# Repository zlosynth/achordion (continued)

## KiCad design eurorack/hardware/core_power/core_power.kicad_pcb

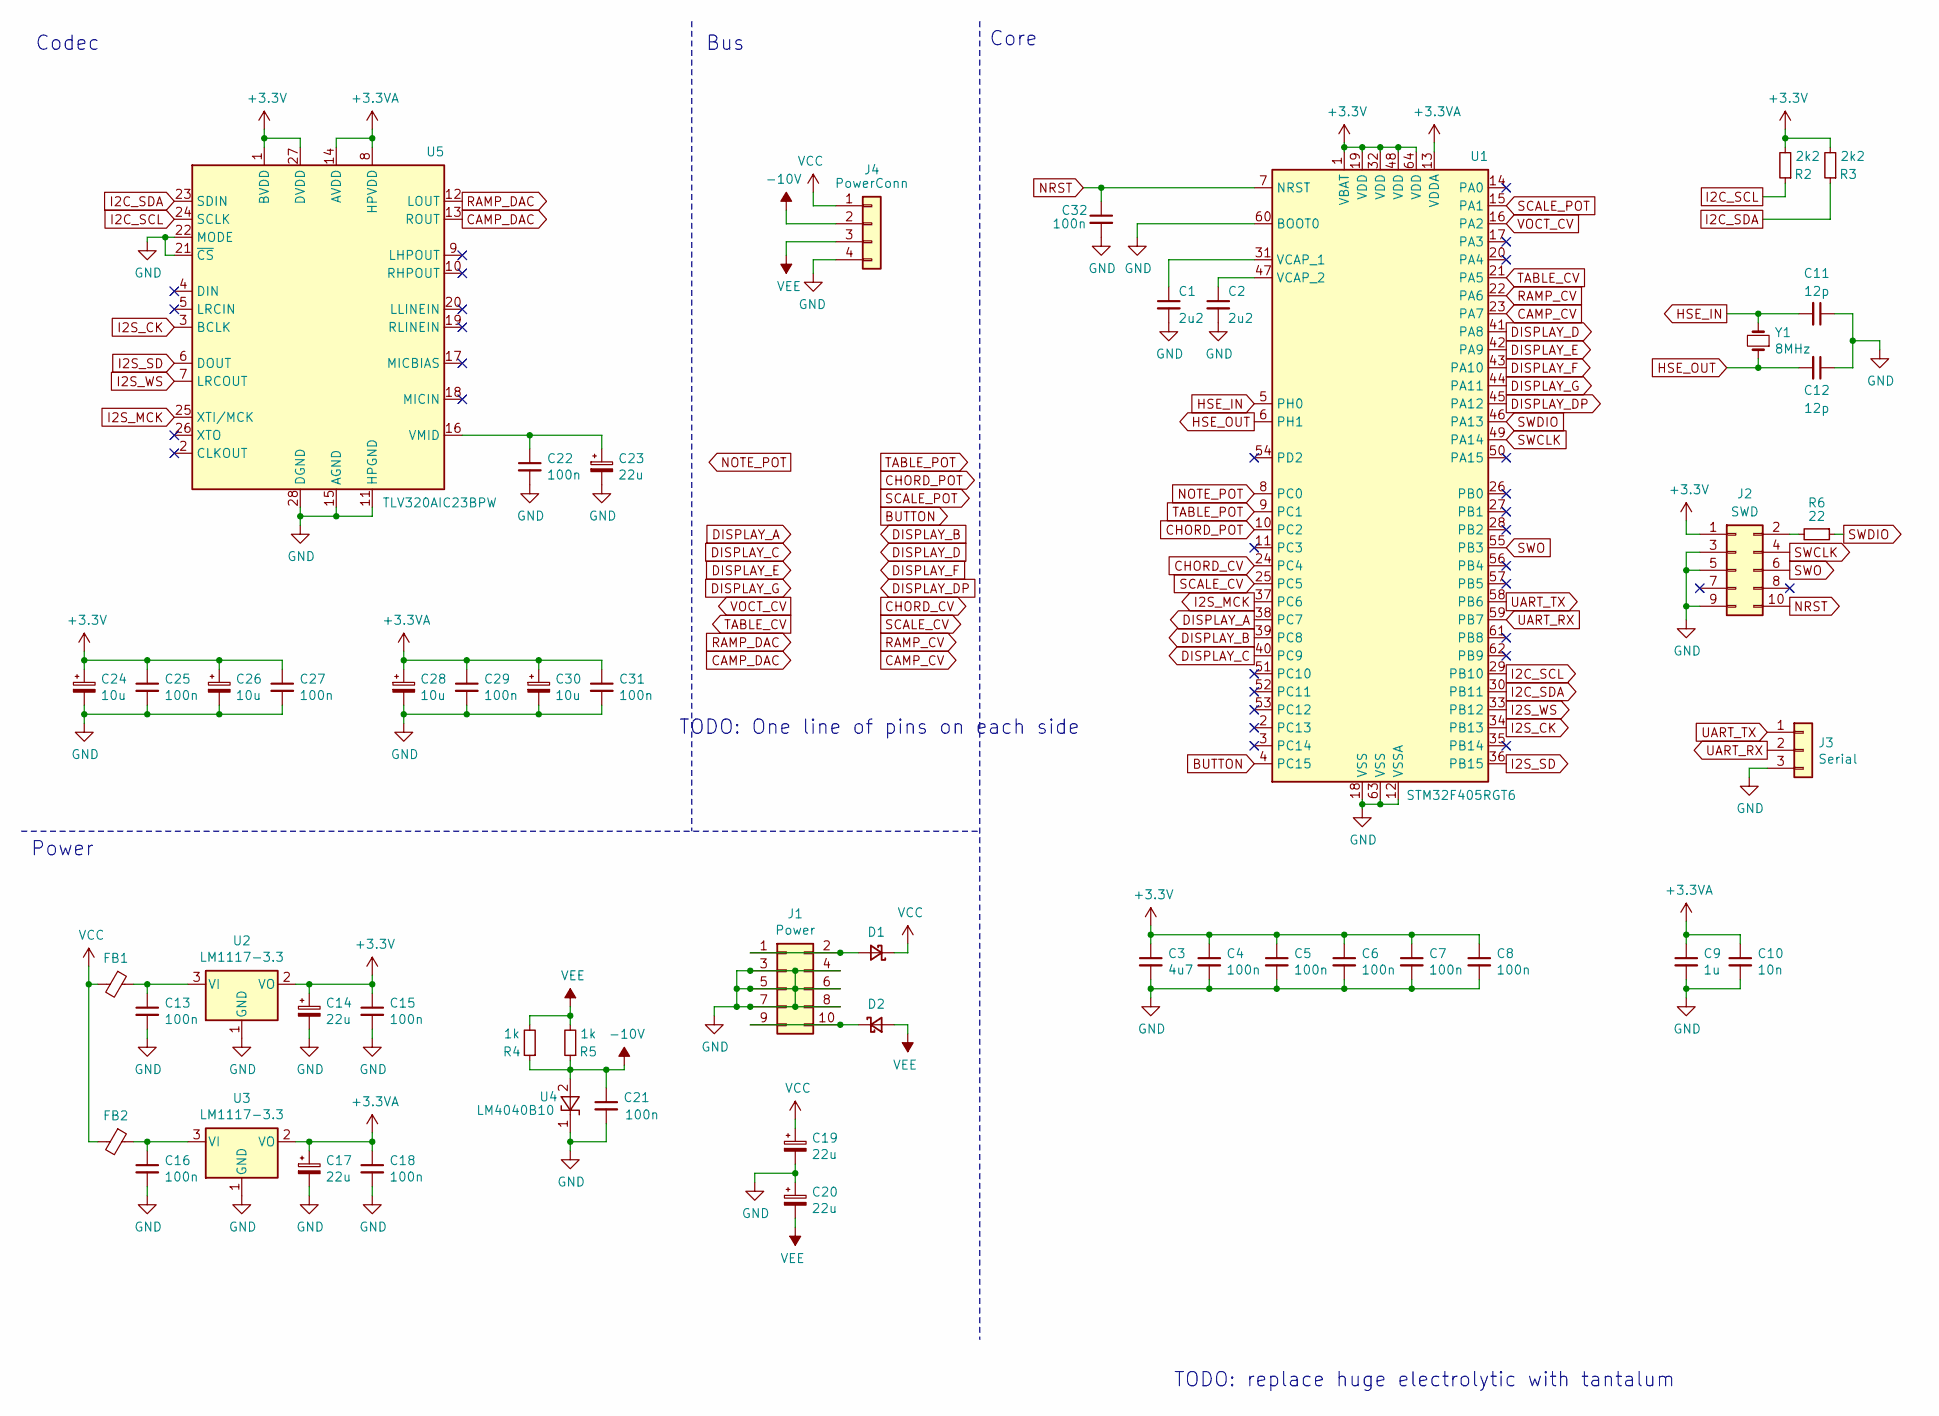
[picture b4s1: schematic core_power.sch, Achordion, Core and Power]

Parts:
C1, C2: 2u2; C_0603_1608Metric
C3: 4u7; C_0603_1608Metric
C4, C5, C6, C7, C8, C15, C18, C22, C25, C27, C29, C31, C32: 100n; C_0402_1005Metric
C9: 1u; C_0603_1608Metric
C10: 10n; C_0402_1005Metric
C11, C12: 12p; C_0402_1005Metric
C13, C16, C21: 100n; C_1206_3216Metric
C14, C17, C19, C20, C23: 22u; CP_Elec_6.3x5.4
C24, C26, C28, C30: 10u; CP_Elec_4x5.7
D1, D2: D_Schottky_Small; D_SOD-123
FB1, FB2: Any; L_0603_1608Metric
J1: Power; IDC-Header_2x05_P2.54mm_Vertical
J2: SWD; PinHeader_2x05_P2.54mm_Vertical_SMD
J3: Serial; PinHeader_1x03_P2.54mm_Vertical_SMD_Pin1Left
J4: PowerConn; PinHeader_1x04_P2.54mm_Vertical
R2, R3: 2k2; R_0402_1005Metric
R4, R5: 1k; R_0603_1608Metric
R6: 22; R_0402_1005Metric
U1: STM32F405RGT6; LQFP-64_10x10mm_P0.5mm
U2, U3: LM1117-3.3; SOT-223-3_TabPin2
U4: LM4040B10; SOT-23
U5: TLV320AIC23BPW; TSSOP-28_4.4x9.7mm_P0.65mm
Y1: 8MHz; Crystal_SMD_3215-2Pin_3.2x1.5mm

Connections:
+3.3VA: C9.1, C10.1, C17.1, C18.1, C28.1, C29.1, C30.1, C31.1, U1.13 (VDDA), U3.2 (VO), U5.8 (HPVDD), U5.14 (AVDD)
+3V3: C3.1, C4.1, C5.1, C6.1, C7.1, C8.1, C14.1, C15.1, C24.1, C25.1, C26.1, C27.1, J2.1, R2.2, R3.2, U1.1 (VBAT), U1.19 (VDD), U1.32 (VDD), U1.48 (VDD), U1.64 (VDD), U2.2 (VO), U5.1 (BVDD), U5.27 (DVDD)
-10V: C21.1, J4.2, R4.1, R5.1, U4.2 (A)
BUTTON: U1.4 (PC15); also elsewhere on the board
CAMP_CV: U1.23 (PA7); also elsewhere on the board
CAMP_DAC: U5.13 (ROUT); also elsewhere on the board
CHORD_CV: U1.24 (PC4); also elsewhere on the board
CHORD_POT: U1.10 (PC2); also elsewhere on the board
DISPLAY_A: U1.38 (PC7); also elsewhere on the board
DISPLAY_B: U1.39 (PC8); also elsewhere on the board
DISPLAY_C: U1.40 (PC9); also elsewhere on the board
DISPLAY_D: U1.41 (PA8); also elsewhere on the board
DISPLAY_DP: U1.45 (PA12); also elsewhere on the board
DISPLAY_E: U1.42 (PA9); also elsewhere on the board
DISPLAY_F: U1.43 (PA10); also elsewhere on the board
DISPLAY_G: U1.44 (PA11); also elsewhere on the board
GND: C1.2, C2.2, C3.2, C4.2, C5.2, C6.2, C7.2, C8.2, C9.2, C10.2, C11.1, C12.1, C13.2, C14.2, C15.2, C16.2, C17.2, C18.2, C19.2, C20.1, C21.2, C22.2, C23.2, C24.2, C25.2, C26.2, C27.2, C28.2, C29.2, C30.2, C31.2, C32.2, J1.3, J1.4, J1.5, J1.6, J1.7, J1.8, J2.3, J2.5, J2.9, J3.3, J4.4, U1.12 (VSSA), U1.18 (VSS), U1.60 (BOOT0), U1.63 (VSS), U2.1 (GND), U3.1 (GND), U4.1 (K), U5.11 (HPGND), U5.15 (AGND), U5.21 (~CS~), U5.22 (MODE), U5.28 (DGND)
HSE_IN: C11.2, U1.5 (PH0), Y1.2
HSE_OUT: C12.2, U1.6 (PH1), Y1.1
I2C_SCL: R2.1, U1.29 (PB10), U5.24 (SCLK)
I2C_SDA: R3.1, U1.30 (PB11), U5.23 (SDIN)
I2S_CK: U1.34 (PB13), U5.3 (BCLK)
I2S_MCK: U1.37 (PC6), U5.25 (XTI/MCK)
I2S_SD: U1.36 (PB15), U5.6 (DOUT)
I2S_WS: U1.33 (PB12), U5.7 (LRCOUT)
NOTE_POT: U1.8 (PC0); also elsewhere on the board
NRST: C32.1, J2.10, U1.7 (NRST)
unnamed: C1.1, U1.31 (VCAP_1)
unnamed: C2.1, U1.47 (VCAP_2)
unnamed: C13.1, FB1.1, U2.3 (VI)
unnamed: C16.1, FB2.1, U3.3 (VI)
unnamed: C22.1, C23.1, U5.16 (VMID)
unnamed: D1.2 (A), J1.1, J1.2
unnamed: D2.1 (K), J1.9, J1.10
unnamed: J2.2, R6.2
RAMP_CV: U1.22 (PA6); also elsewhere on the board
RAMP_DAC: U5.12 (LOUT); also elsewhere on the board
SCALE_CV: U1.25 (PC5); also elsewhere on the board
SCALE_POT: U1.15 (PA1); also elsewhere on the board
SWCLK: J2.4, U1.49 (PA14)
SWDIO: R6.1, U1.46 (PA13)
SWO: J2.6, U1.55 (PB3)
TABLE_CV: U1.21 (PA5); also elsewhere on the board
TABLE_POT: U1.9 (PC1); also elsewhere on the board
UART_RX: J3.2, U1.59 (PB7)
UART_TX: J3.1, U1.58 (PB6)
VCC: C19.1, D1.1 (K), FB1.2, FB2.2, J4.1
VEE: C20.2, D2.2 (A), J4.3, R4.2, R5.2
VOCT_CV: U1.16 (PA2); also elsewhere on the board

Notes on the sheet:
Bus
Codec
TODO: replace huge electrolytic with tantalum
Core
Power
TODO: One line of pins on each side

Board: 4 copper layers, 52 parts (0 on the bottom side), 49 nets, no tracks yet.

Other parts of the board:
J5: SignalConn; PinHeader_2x12_P2.54mm_Vertical

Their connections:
BUTTON: J5.8; also elsewhere on the board
CAMP_CV: J5.24; also elsewhere on the board
CAMP_DAC: J5.23; also elsewhere on the board
CHORD_CV: J5.18; also elsewhere on the board
CHORD_POT: J5.4; also elsewhere on the board
DISPLAY_A: J5.9; also elsewhere on the board
DISPLAY_B: J5.10; also elsewhere on the board
DISPLAY_C: J5.11; also elsewhere on the board
DISPLAY_D: J5.12; also elsewhere on the board
DISPLAY_DP: J5.16; also elsewhere on the board
DISPLAY_E: J5.13; also elsewhere on the board
DISPLAY_F: J5.14; also elsewhere on the board
DISPLAY_G: J5.15; also elsewhere on the board
NOTE_POT: J5.1; also elsewhere on the board
RAMP_CV: J5.22; also elsewhere on the board
RAMP_DAC: J5.21; also elsewhere on the board
SCALE_CV: J5.20; also elsewhere on the board
SCALE_POT: J5.6; also elsewhere on the board
TABLE_CV: J5.19; also elsewhere on the board
TABLE_POT: J5.2; also elsewhere on the board
VOCT_CV: J5.17; also elsewhere on the board

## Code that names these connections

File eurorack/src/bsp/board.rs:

use stm32h7xx_hal as hal;

use super::pins::*;

static mut TAKEN: bool = false;

pub struct Board;

impl Board {
    #[inline]
    pub fn take() -> Option<Self> {
        cortex_m::interrupt::free(|_| if unsafe { TAKEN } { None } else { Some(Board) })
    }

    pub fn split_gpios(
        &self,
        gpioa: hal::gpio::gpioa::Parts,
        gpiob: hal::gpio::gpiob::Parts,
        gpioc: hal::gpio::gpioc::Parts,
        gpiod: hal::gpio::gpiod::Parts,
    ) -> Pins {
        Pins {
            PIN_BUTTON: gpiob.pb4.into_pull_up_input(),
            PIN_CV1: gpioc.pc1,
            PIN_CV2: gpioa.pa6,
            PIN_CV3: gpioc.pc0,
            PIN_CV4: gpioa.pa3,
            PIN_CV5: gpiob.pb1,
            PIN_CV6: gpioa.pa7,
            PIN_LED1: gpiob.pb15,
            PIN_LED2: gpiob.pb14,
            PIN_LED3: gpiod.pd11,
            PIN_LED4: gpioa.pa0,
            PIN_LED5: gpioc.pc9,
            PIN_LED6: gpioc.pc8,
            PIN_LED7: gpiod.pd2,
            PIN_LED8: gpioc.pc12,
            PIN_POT1: gpioa.pa4,
            PIN_POT2: gpioa.pa1,
            PIN_POT3: gpioa.pa5,
            PIN_POT4: gpioc.pc4,
            PIN_PROBE: gpiob.pb5,

            LED_USER: gpioc.pc7,
        }
    }
}

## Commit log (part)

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2021-08-01 Remove component labels from the silkscreen
    Prefer cleanliness. For manufacturing, print PDFs with all the
    components and their values spelled out in bigger letters - plus one can
    cross them out.
2021-08-02 Replace DAC decoupling cap with LPF
    The design with big decoupling cap was taken from WM8731 used for
    Elements. However, with AK4556 used in Daisy Seed, it is not needed (or
    at least not a part of the datasheet), instead, use LPF for ~70 kHz.
2021-08-02 Remove unused reserved interrupt
2021-08-03 Move peripheral abstractions to their own modules
2021-08-04 Rename adc1 attribute to adc
    In interface abstraction, it does not matter which ADC of the MCU it is.
2021-08-04 Transpose LED order of PCB to logical
    While the PCB numbers the LEDs as following:
    1 5
    2 6
    3 7
    4 8
    Their values with respect to degrees of scale are treated as following:
2021-08-05 Hide audio interface details behind an abstraction
2021-08-05 Refactor storage logic outside eurorack main
2021-08-06 Move input activity to its own module
2021-08-06 Put audio interface fully behind an abstraction
2021-08-09 Align user labels on the PCB schema
    With this, labels and outlines can be printed to help with soldering.
2021-08-09 Use 10uF for decoupling caps
    This value seems to be more common in stores. It should not matter if 22
    or 10 is used, so let's go with the common one.
2021-08-10 Adjust wording in the Changelog README
2021-08-10 Adjust plot script to align with the one in kicad
    These updates are based around:
    https://github.com/KiCad/kicad-source-mirror/blob/5.1/demos/python_scripts_examples/gen_gerber_and_drill_files_board.py
2021-08-10 Add sleep before exiting eeschema
    It sometimes need little while before it is ready to accept the exit
    command.
2021-08-17 Add assembly labels for pots and leds
2021-08-19 Apply black formatting on python scripts
2021-08-22 Move hardware scripts under hack
    Plotting is already there, so move this too.
2021-08-23 Explicitly select Python scripts to test
    Without this, CI tries to test plot_pcb.py, which ends up failing due to
    a missing dependency. There is no test available in that script, so
    let's skip it.
2021-08-25 Rise temporary VCA gate CV
    With the change of CVs, this needs to be adjusted too.
2021-08-29 Remove amplitude control
    This option was used only testing while I did not have a VCA. Now I do!
2021-08-29 Release version 0.10.0
2021-09-01 Add temporary profiling macros
2021-09-08 Use second ADC for CV handling
    This is a preparation step before both ADCs are used simultaneously.
2021-09-08 Lower the sample time of ADC to 1/4
    This seems to be still plenty to provide stable output while it saves a
    lot of time. In a follow-up patch, the frequency of the control loop
    will be increased to compensate for it.
2021-09-09 Simplify jack probe detection
    With this new approach, the probe generator and detector must be
    synchronized on the same beat, that makes orchestration little more
    clunky. However, it leads into major performance improvement. Instead of
    7% of MCU, the detection now takes almost nothing.
2021-09-10 Add third set of profiling macros
    This allows using three probes at once.
2021-09-11 Quantize all scales to white keys
    Align all quantization with white keys. All scales can be now played
    through white keys only, with black keys always quantizing to the
    previous white.
2021-09-12 Introduce CV calibration mode
    When the button it held down and a jack gets plugged to the V/OCT input,
    the module enters calibration mode. In that, C should be played on the
    input device, then button clicked, then C one octave higher and one
    click again. After that, calibration is done and input keys should be
    preciselly mapped and quantized.
2021-09-12 Gracefully handle invalid calibration input
    If the input is too close nearby, ignore it as an error, possibly a
    double click while calibrating or attempt to cancel it.
2021-09-12 Allow reset of all stored parameters on boot
    If the button is held down while booting, all stored parameters (alt
    values and calibration) will be erased.
2021-09-14 Fix input activity handling
    There were bugs that caused the display not to get updated when pot
    movement was too slow to be detected, seems like. With this, the display
    reacts better.
2021-09-14 Increase detune phase on display lineary
2021-09-17 Add changelog for 4th solo voice
2021-09-18 Display state of the forth voice
2021-09-19 State that 1% parts must be used around CV1,2
    These CVs are used for precise V/OCT input.
2021-09-24 Rebase on newly merged HAL changes
    The eurorack module depends on some WIP PRs. Some of them [1] was merged
    and this patch starts consuming it.
    [1] https://github.com/stm32-rs/stm32h7xx-hal/pull/250
2021-09-24 Increase optimization level
    Now with much of the flash saved by wavetables bandlimited on runtime,
    optimization for performance can be enabled again. This gives following
    improvements: DSP cycle takes 28% instead of 48%.
2021-09-25 Move scale mode control to pot 4
    This frees up alternative mode of pot 3 for configuration of play mode.
2021-09-25 Fix instrument chord test
2021-09-25 Show selected play style on the display
2021-09-25 Add wider chords to the first play style
    These will be crispier when played with ritcher waveforms.
2021-09-26 Extend number of chord degrees to 5
    Increase the maximum number of chord degrees to 5 and populate the
    default chord style with some nineth chords.
2021-09-28 Release version 0.14.0
2021-09-28 Perform initialization in a separate task
    With this patch, slow instrment initialization was moved out of the init
    function into a separate task. This new task runs parallel to DSP
    handling.
    This change unexplicably made startup faster and also allows use of the
    setup progress display without audio pop.
2021-09-29 Show progress on boot display
    Instead of animation, show the real progress through banks.
2021-09-30 Replace vowel bank with sin multiple+sum sequences
2021-10-01 Document how to measure firmware size
2021-10-02 Make it possible to select bandlimiting algorithm
    Bandlimiting is available with two different filtering algorithms - fast
    fourier transform (FFT) removing high frequency bins and state variable
    filter (SVF). While FFT provides crips clean and very sharp sound, SVF
    goes little harder on filtering and leaves slighly more muted, but
    warmer sound. Preferred algorithm can be selected through a feature in
    `Cargo.toml` of both Eurorack and Pure Data modules.
2021-10-02 Release version 0.15.0
2021-10-02 Detune schould affect less each octave below
    The same relative frequency change one octave below is twice as
    significant two octaves below. Reflect it in the detune.
2021-10-03 Instead of high frequency filtering, generate sine
2021-10-07 Remove unnecessary conversion to i32
2021-10-07 Pre-calculate niquist
2021-10-09 Traverse wavetable changes between CV reconciles.
    This prevents noise during changes of wavetables without many harmonics,
    due to abrupt changes between CV intevals.
2021-10-10 Assert correct linear_xfade arguments on testing
2021-10-10 Center the mean of sin multiples
    Some of these wavetables are not centered around 0 and thus when played
    in a chord with detune, they get very far of the equilibrium and produce
    pops. This forces them to center.
2021-10-10 Simplify amplitude handling
2021-10-13 Compensate amplitude of low numbers of oscillators
    With this, the overal loudness should be more balanced between 1 and 18
    oscillators being used.
2021-10-27 Wire compatibility version into the PCB
    4 GPIO pins will be signaling version of the hardware to software. This
    will allow the software to remain backwards compatible to some degree.
2021-11-18 Add a manual
    This manual is made through latex. It can be rendered as a PDF both for
    digital use and for printing.
2021-11-18 Extend manual gitignore
2021-11-19 Move development guide out of the README
2021-12-10 Adjust firmware to the new pinout
2021-12-11 Add a make target to update dependencies
2021-12-12 Increase display sensitivity to CV
    So it shows even small changes of input.
2021-12-12 Stabilize the display against blinking
    Perform averaging on the display state.
2021-12-13 Improve the optimization level to avoid noise
    With level 2, the hardware is not keeping up and noise gets into the
    output.
2021-12-14 Add mounting holes for distancing standoffs
    This will make the two PCBs less wobbly.
2021-12-15 Enable control of quantization on the side line
2021-12-15 Document the depth of the module
2021-12-16 State that all CV scaling resistors should be 1%
2021-12-17 Fix bit noise of uninitialized voices
2021-12-18 Remove output attenuation
    These values should be within limits of -1.0 to 1.0. Furthermore, they
    should not be clipping on the output as the output is amplified to
    10 Vpp.
2021-12-18 Fix the website link
2022-01-28 Introduce a build manual
2022-02-01 Remove amplitude balancing on small chords
    With this, every oscillator is given the same amplitude. This guarantees
    that all tones will keep their continuous loudness and with that fixes
    an issue where change of size of a chord would weaken continuous tones
    kept between chords, e.g. the root. The downside of this is that small
    chords and solo tones have much weaker signal.
2022-02-03 Release version 1.3.0
2022-02-03 Resolve a bug where chord replaces silenced solo
    The original code did not recognize difference between unpugged solo and
    solo with CV input under 0. This is now fixed.
2022-02-05 Move I/O operations outside the instrument lock
    With this patch, operating of GPIO is handled only once the intrument
    lock is released. Thanks to that, all operations done with the lock are
    purely internal and should not block the DSP thread.
2022-02-24 Define a footprint for Daisy Patch SM
2022-03-19 Simplify boolean evaluation in input_activity
2022-03-19 Fix backup to start from the latest version
2022-03-20 Git ignore KiCad backup files
2022-03-26 Increase font of notes on PCB
2022-03-29 Update build manual drawing with new labels
2022-04-16 Emphasize to be careful while detaching SM
2022-04-22 Switch to Daisy Patch SM
2022-04-22 Move power connector so USB can be plugged in
2022-04-23 Mention the video in the readme
2022-04-23 Fix the release script
2022-04-23 Add BAT54S to the manufacture list
2022-04-23 Add a script for easy updates of the website
2022-04-26 Adjust CHORD V/oct offset to -5 +5V
2022-04-29 Note that pot washers are tight
2022-04-29 Fix english in the build manual
2022-05-19 Run the user manual through a grammar analyzer
2022-07-13 Introduce harmonic minor mode
2022-07-13 Fix manual mention of double blink
2022-07-13 Add mail contact to user manual
2022-07-17 Save 1kB of flash by inlining some functions
2022-07-17 Leave micromath optimized
    It is used in DSP for overdrive.
2022-07-18 Allow remapping of CV inputs to select scale
2022-07-18 Add release note about scale control to manual
2022-07-19 Release version 2.2.0
2022-07-24 Add make target cleaning old artifacts
    Rust pre-builds can take GBs of space.
2022-07-25 Make scale mode CV consistent
    Handle offsetting the same way it is done for other attributes.
2022-07-31 Use token to invalidate incompatible backups
2022-07-31 Remove Pure Data externals
    They are moved to https://github.com/zlosynth/automaton.
2022-11-04 Use Rust 1.63 on CI as well
    This is following the DEVELOPMENT.md documentation.
2023-09-26 Update KiCAD version
2023-09-26 List more viable capacitors
2023-09-30 Revert "Remove WEEE and CE from public repo"
    This reverts commit efba61ae0437d9b1e39a988e139de775eaaddcb0.
2024-06-16 Simplify save conversion to bytes
    Transmute should be safe to used in this case, since the same program
    that writes the bytes is also reading them.
    This frees a little bit of flash to accomodate for follow-up patches.
2024-10-05 Update build manual for no foil knobs
2024-11-24 Improve tuning even further
2024-11-25 Bump store token
2025-10-16 Fix release notes and quantization feature name
2026-01-26 Revert "Add pickup mode for primary controls"
    This reverts commit f9e11310530916c7bc6734e40a8152c87b93300b.
